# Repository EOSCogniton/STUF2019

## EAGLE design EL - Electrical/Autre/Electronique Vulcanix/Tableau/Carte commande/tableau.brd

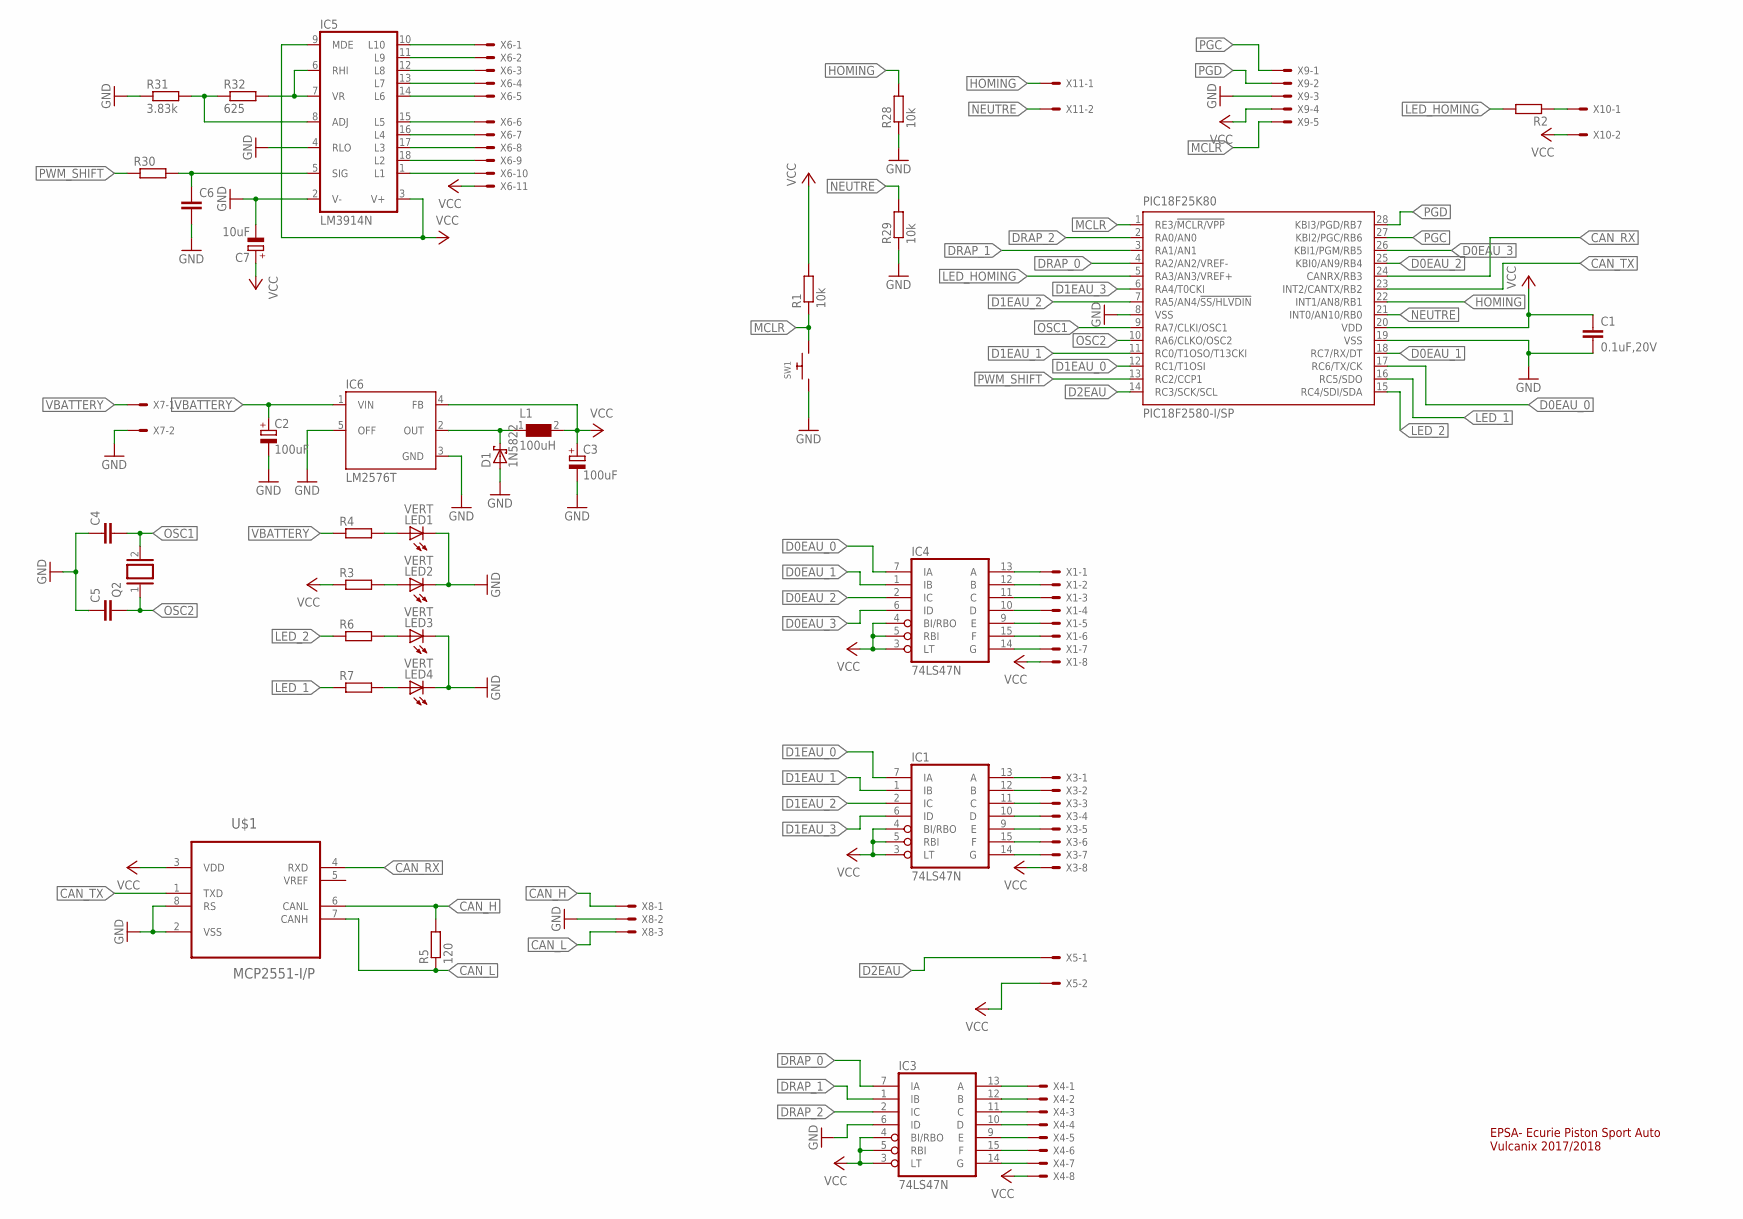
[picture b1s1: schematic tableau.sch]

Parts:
C1: 0.1uF,20V; C025-025X050
C2, C3: 100uF; E2-5
C4, C5: C-EU025-030X050; C025-030X050
C6: C-EU025-025X050; C025-025X050
C7: 10uF; E2-5
D1: 1N5822; DO201T15
IC1, IC3, IC4: 74LS47N; DIL16
IC5: LM3914N; DIL18
IC6: LM2576T; TO220-5
L1: 100uH; WE-TI_8012B
LED1, LED2, LED3, LED4: VERT; LED3MM
PIC18F25K80: PIC18F2580-I/SP; DIL28-3
Q2: XTAL/S; QS
R1, R28, R29: 10k; 0204/7
R2, R3, R4, R6, R7, R30: R-EU_0204/7; 0204/7
R5: 120; 0204/7
R31: 3.83k; 0204/7
R32: 625; 0204/7
SW1: SWITCH_PUSHBUTTONSOFTTOUCHSMD_SJ; PUSHBUTTON_SMD_SJ
U$1: MCP2551-I/P; DIP254P762X432-8
X1, X3, X4: KK-156-8
X5, X7, X10, X11: KK-156-2
X6: KK-156-11
X8: KK-156-3
X9: KK-156-5

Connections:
CAN_H: R5.2, U$1.6 (CANL), X8.1
CAN_L: R5.1, U$1.7 (CANH), X8.3
CAN_RX: PIC18F25K80.24 (CANRX/RB3), U$1.4 (RXD)
CAN_TX: PIC18F25K80.23 (INT2/CANTX/RB2), U$1.1 (TXD)
D0EAU_0: IC4.7 (IA), PIC18F25K80.17 (RC6/TX/CK)
D0EAU_1: IC4.1 (IB), PIC18F25K80.18 (RC7/RX/DT)
D0EAU_2: IC4.2 (IC), PIC18F25K80.25 (KBI0/AN9/RB4)
D0EAU_3: IC4.6 (ID), PIC18F25K80.26 (KBI1/PGM/RB5)
D1EAU_0: IC1.7 (IA), PIC18F25K80.12 (RC1/T1OSI)
D1EAU_1: IC1.1 (IB), PIC18F25K80.11 (RC0/T1OSO/T13CKI)
D1EAU_2: IC1.2 (IC), PIC18F25K80.7 (RA5/AN4/!SS/HLVDIN)
D1EAU_3: IC1.6 (ID), PIC18F25K80.6 (RA4/T0CKI)
D2EAU: PIC18F25K80.14 (RC3/SCK/SCL), X5.1
DRAP_0: IC3.7 (IA), PIC18F25K80.4 (RA2/AN2/VREF-)
DRAP_1: IC3.1 (IB), PIC18F25K80.3 (RA1/AN1)
DRAP_2: IC3.2 (IC), PIC18F25K80.2 (RA0/AN0)
GND: C1.2, C2.-, C3.-, C4.1, C5.1, C6.2, C7.-, D1.A, IC1.8 (GND), IC3.6 (ID), IC3.8 (GND), IC4.8 (GND), IC5.2 (V-), IC5.4 (RLO), IC6.3 (GND), IC6.5 (OFF), LED1.K (C), LED2.K (C), LED3.K (C), LED4.K (C), PIC18F25K80.8 (VSS), PIC18F25K80.19 (VSS), R28.1, R29.1, R31.1, SW1.P$1, U$1.2 (VSS), U$1.8 (RS), X7.2, X8.2, X9.3
HOMING: PIC18F25K80.22 (INT1/AN8/RB1), R28.2, X11.1
LED_1: PIC18F25K80.16 (RC5/SDO), R7.1
LED_2: PIC18F25K80.15 (RC4/SDI/SDA), R6.1
LED_HOMING: PIC18F25K80.5 (RA3/AN3/VREF+), R2.2
MCLR: PIC18F25K80.1 (RE3/!MCLR/VPP), R1.1, SW1.P$2, X9.5
unnamed: LED1.A, R4.2
unnamed: IC4.13 (A), X1.1
unnamed: LED2.A, R3.2
unnamed: R2.1, X10.1
unnamed: IC4.12 (B), X1.2
unnamed: IC4.11 (C), X1.3
unnamed: IC4.10 (D), X1.4
unnamed: IC4.9 (E), X1.5
unnamed: IC4.15 (F), X1.6
unnamed: IC4.14 (G), X1.7
unnamed: IC1.13 (A), X3.1
unnamed: IC1.12 (B), X3.2
unnamed: IC1.11 (C), X3.3
unnamed: IC1.10 (D), X3.4
unnamed: IC1.9 (E), X3.5
unnamed: IC1.15 (F), X3.6
unnamed: IC1.14 (G), X3.7
unnamed: IC3.13 (A), X4.1
unnamed: IC3.12 (B), X4.2
unnamed: IC3.11 (C), X4.3
unnamed: IC3.10 (D), X4.4
unnamed: IC3.9 (E), X4.5
unnamed: IC3.15 (F), X4.6
unnamed: IC3.14 (G), X4.7
unnamed: IC5.10 (L10), X6.1
unnamed: IC5.11 (L9), X6.2
unnamed: IC5.12 (L8), X6.3
unnamed: IC5.13 (L7), X6.4
unnamed: IC5.14 (L6), X6.5
unnamed: IC5.15 (L5), X6.6
unnamed: IC5.16 (L4), X6.7
unnamed: IC5.17 (L3), X6.8
unnamed: IC5.18 (L2), X6.9
unnamed: IC5.1 (L1), X6.10
unnamed: LED3.A, R6.2
unnamed: LED4.A, R7.2
unnamed: C6.1, IC5.5 (SIG), R30.2
unnamed: IC5.6 (RHI), IC5.7 (VR), R32.2
unnamed: IC5.8 (ADJ), R31.2, R32.1
unnamed: D1.C, IC6.2 (OUT), L1.1
NEUTRE: PIC18F25K80.21 (INT0/AN10/RB0), R29.2, X11.2
OSC1: C4.2, PIC18F25K80.9 (RA7/CLKI/OSC1), Q2.2
OSC2: C5.2, PIC18F25K80.10 (RA6/CLKO/OSC2), Q2.1
PGC: PIC18F25K80.27 (KBI2/PGC/RB6), X9.1
PGD: PIC18F25K80.28 (KBI3/PGD/RB7), X9.2
PWM_SHIFT: PIC18F25K80.13 (RC2/CCP1), R30.1
VBATTERY: C2.+, IC6.1 (VIN), R4.1, X7.1
VCC: C1.1, C3.+, C7.+, IC1.3 (LT), IC1.4 (BI/RBO), IC1.5 (RBI), IC1.16 (VCC), IC3.3 (LT), IC3.4 (BI/RBO), IC3.5 (RBI), IC3.16 (VCC), IC4.3 (LT), IC4.4 (BI/RBO), IC4.5 (RBI), IC4.16 (VCC), IC5.3 (V+), IC5.9 (MDE), IC6.4 (FB), L1.2, PIC18F25K80.20 (VDD), R1.2, R3.1, U$1.3 (VDD), X1.8, X3.8, X4.8, X5.2, X6.11, X9.4, X10.2

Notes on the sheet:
EPSA- Ecurie Piston Sport Auto Vulcanix 2017/2018

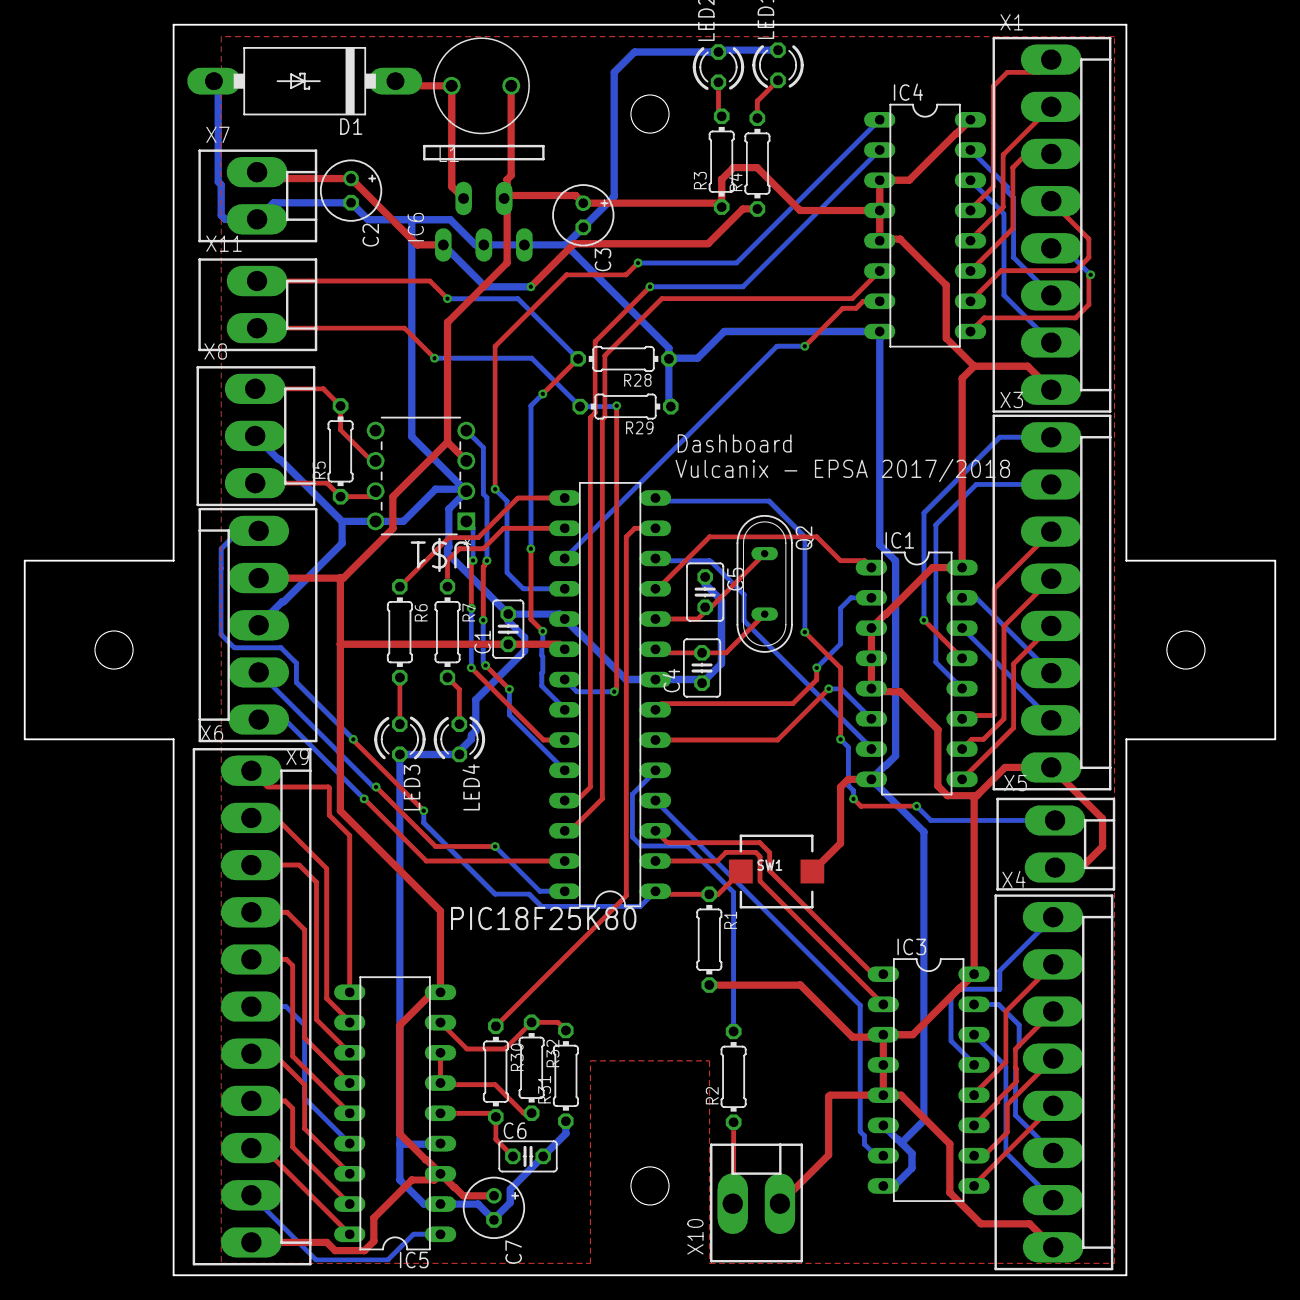
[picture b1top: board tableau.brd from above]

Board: 2 copper layers, 105.0 x 105.0 mm, 44 parts (0 on the bottom side), 70 nets.

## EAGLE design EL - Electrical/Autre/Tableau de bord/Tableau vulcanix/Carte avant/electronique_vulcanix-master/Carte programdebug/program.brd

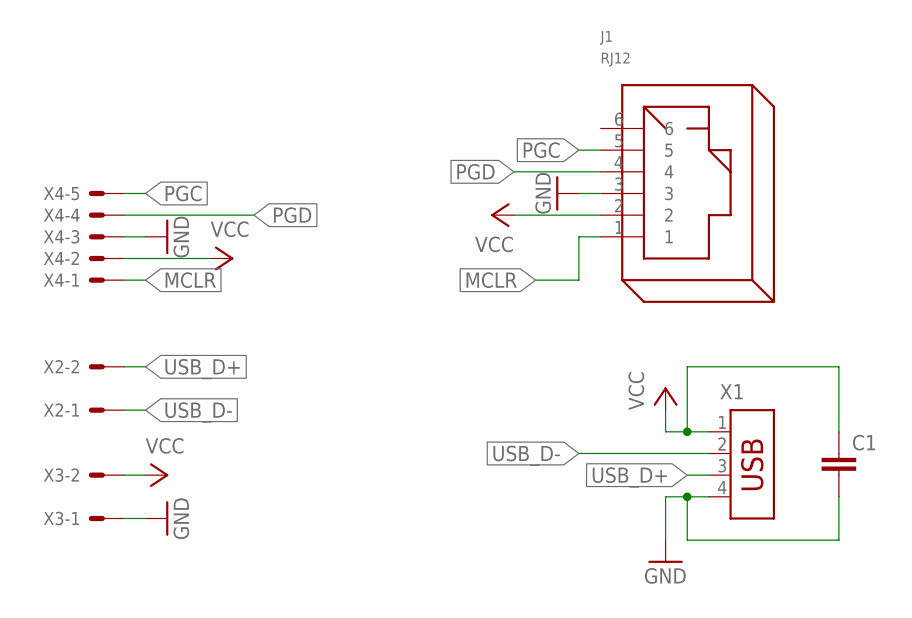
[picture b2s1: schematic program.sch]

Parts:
C1: C-EU025-030X050; C025-030X050
J1: RJ12
X1: USB-787616; USB
X2, X3: KK-156-2
X4: KK-156-5

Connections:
GND: C1.2, J1.3, X1.4, X3.1, X4.3
MCLR: J1.1, X4.1
PGC: J1.5, X4.5
PGD: J1.4, X4.4
USB_D+: X1.3, X2.2
USB_D-: X1.2, X2.1
VCC: C1.1, J1.2, X1.1, X3.2, X4.2

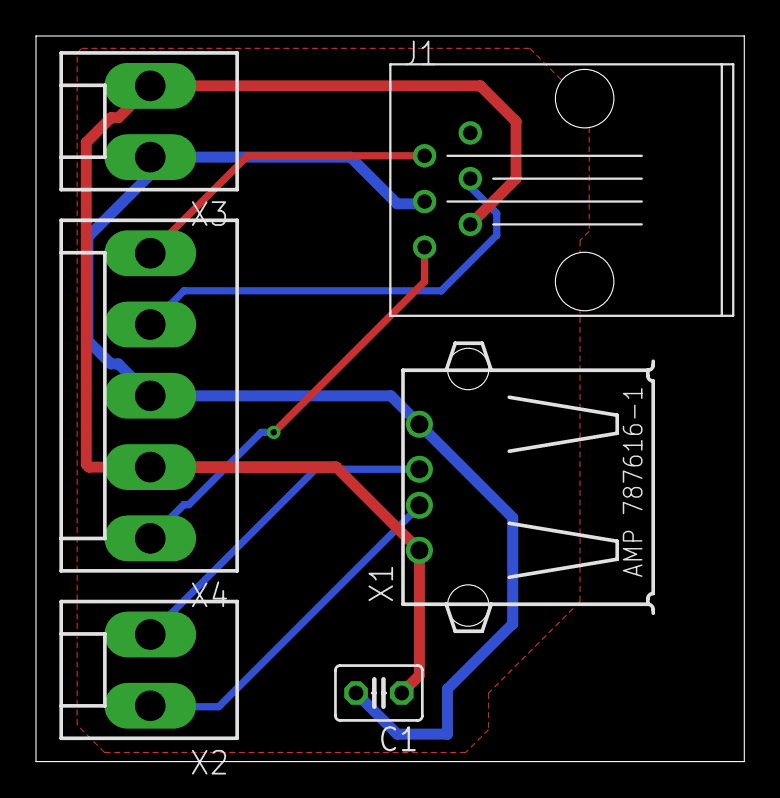
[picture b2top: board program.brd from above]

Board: 2 copper layers, 39.3 x 40.3 mm, 6 parts (0 on the bottom side), 7 nets.

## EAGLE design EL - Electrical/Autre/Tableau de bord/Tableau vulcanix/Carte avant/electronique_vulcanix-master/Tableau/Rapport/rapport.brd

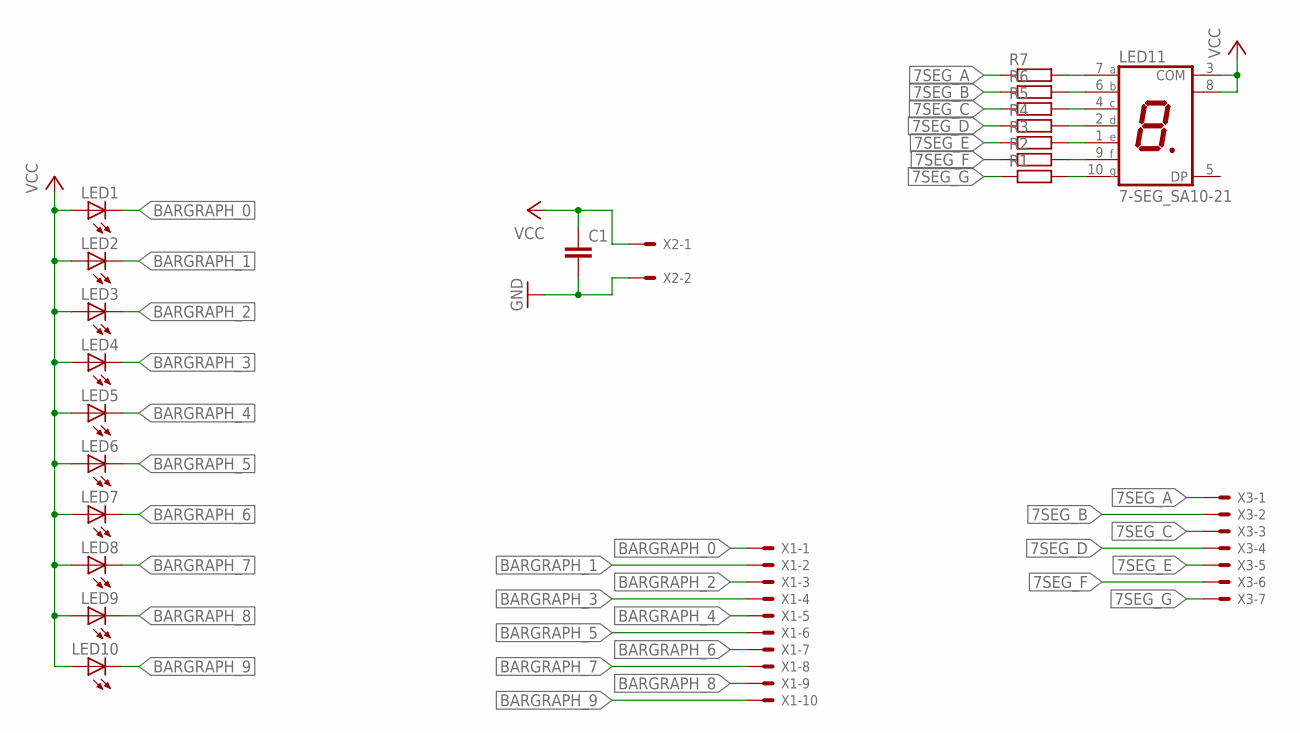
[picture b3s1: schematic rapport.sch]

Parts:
C1: C-EU025-030X050; C025-030X050
LED1, LED2, LED3, LED4, LED5, LED6, LED7, LED8, LED9, LED10: LED5MM
LED11: 7-SEG_SA10-21; SA10-21
R1, R2, R3, R4, R5, R6, R7: R-EU_0204/7; 0204/7
X1: KK-156-10
X2: KK-156-2
X3: KK-156-7

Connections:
7SEG_A: R7.1, X3.1
7SEG_B: R6.1, X3.2
7SEG_C: R5.1, X3.3
7SEG_D: R4.1, X3.4
7SEG_E: R3.1, X3.5
7SEG_F: R2.1, X3.6
7SEG_G: R1.1, X3.7
BARGRAPH_0: LED1.K (C), X1.1
BARGRAPH_1: LED2.K (C), X1.2
BARGRAPH_2: LED3.K (C), X1.3
BARGRAPH_3: LED4.K (C), X1.4
BARGRAPH_4: LED5.K (C), X1.5
BARGRAPH_5: LED6.K (C), X1.6
BARGRAPH_6: LED7.K (C), X1.7
BARGRAPH_7: LED8.K (C), X1.8
BARGRAPH_8: LED9.K (C), X1.9
BARGRAPH_9: LED10.K (C), X1.10
GND: C1.2, X2.2
unnamed: LED11.7 (A), R7.2
unnamed: LED11.6 (B), R6.2
unnamed: LED11.4 (C), R5.2
unnamed: LED11.2 (D), R4.2
unnamed: LED11.1 (E), R3.2
unnamed: LED11.9 (F), R2.2
unnamed: LED11.10 (G), R1.2
VCC: C1.1, LED1.A, LED2.A, LED3.A, LED4.A, LED5.A, LED6.A, LED7.A, LED8.A, LED9.A, LED10.A, LED11.3 (COM), LED11.8 (COM), X2.1

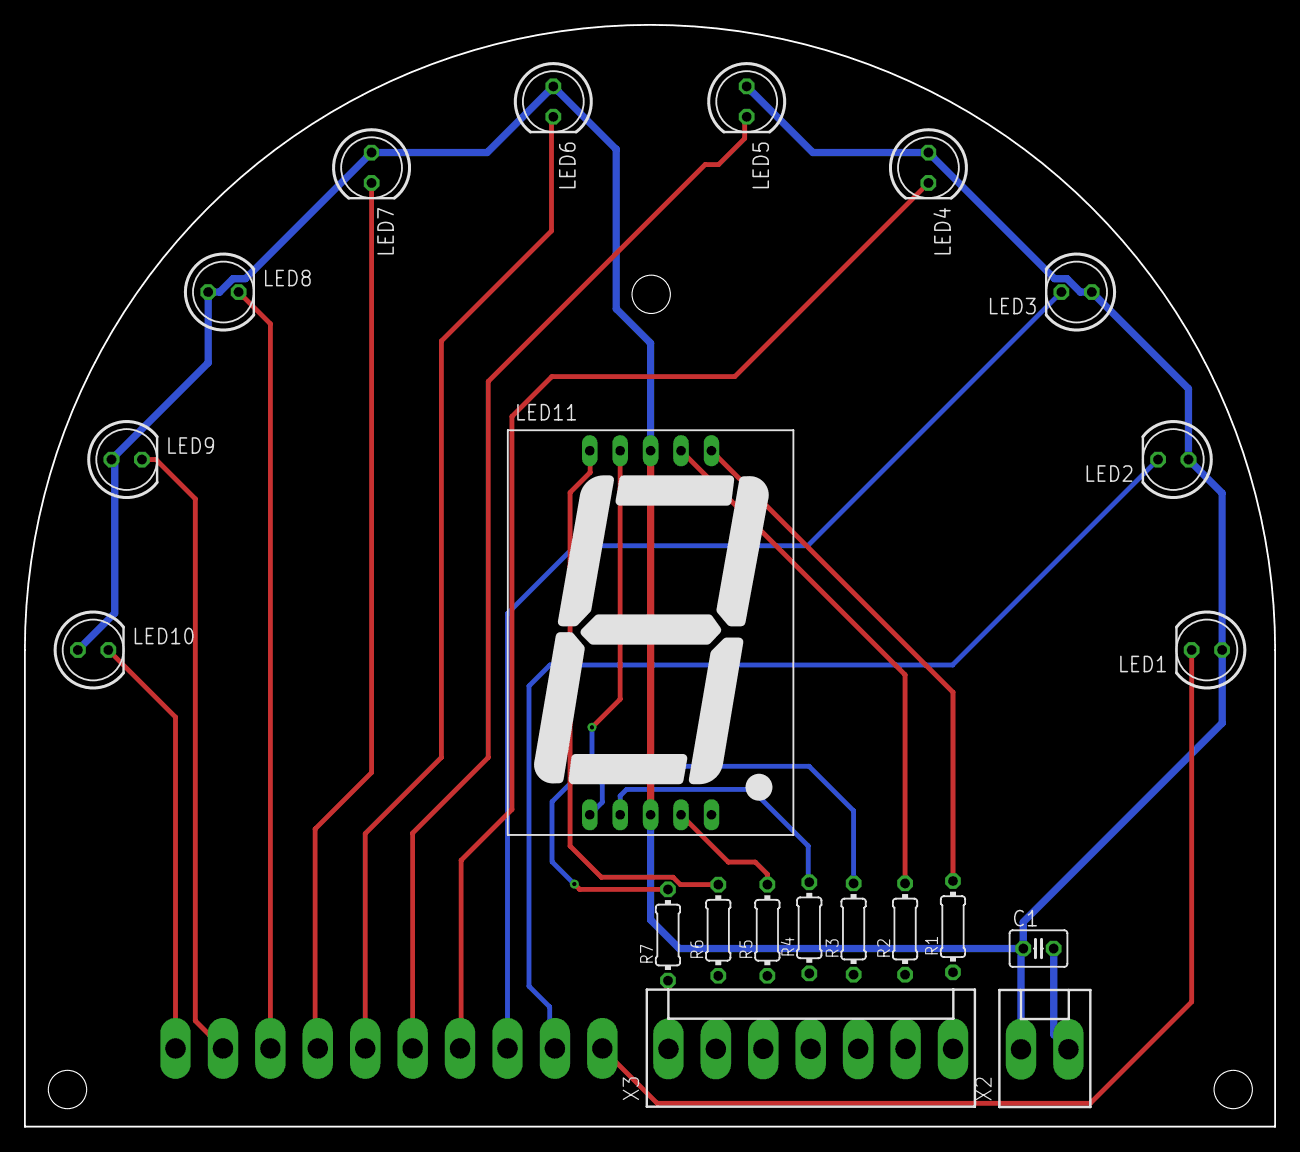
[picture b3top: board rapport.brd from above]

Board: 2 copper layers, 104.4 x 92.0 mm, 22 parts (1 on the bottom side), 26 nets.

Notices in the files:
parts and their libraries:
microbuilder: This work is placed in the public domain, and may be freely used for commercial and non-commercial work with the following conditions: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
